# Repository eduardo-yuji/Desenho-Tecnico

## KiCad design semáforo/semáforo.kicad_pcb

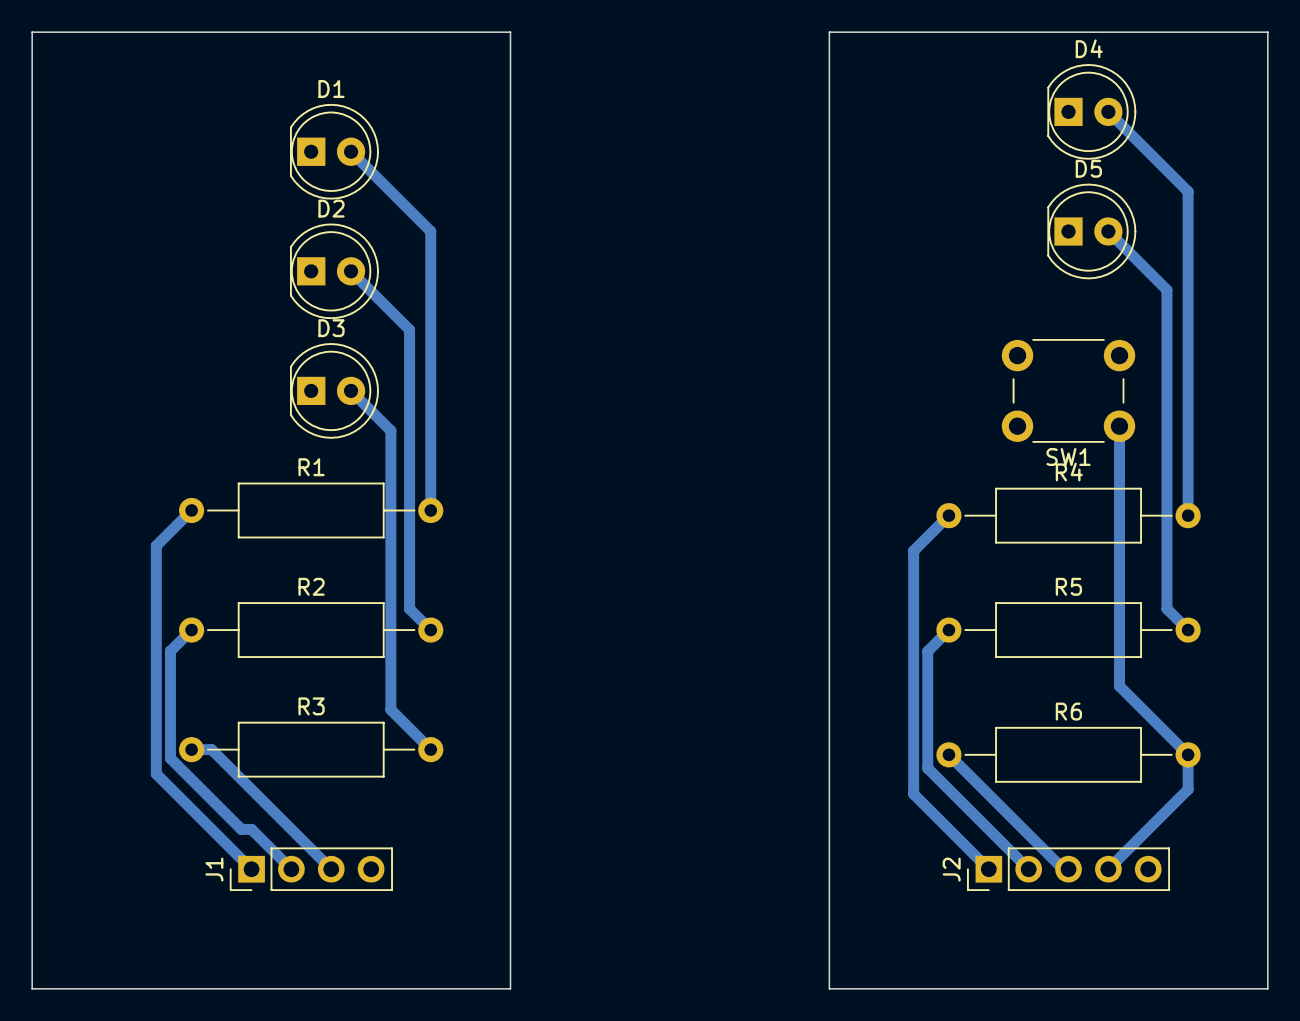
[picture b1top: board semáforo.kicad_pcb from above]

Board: 2 copper layers, 78.7 x 61.0 mm, 14 parts (0 on the bottom side), 13 nets.

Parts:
D1, D2, D3, D4, D5: LED; LED_D5.0mm
J1: Conn_01x04_Male; PinHeader_1x04_P2.54mm_Vertical
J2: Conn_01x05_Male; PinHeader_1x05_P2.54mm_Vertical
R1, R2, R3, R4, R5, R6: R; R_Axial_DIN0309_L9.0mm_D3.2mm_P15.24mm_Horizontal
SW1: SW_Push; SW_PUSH_6mm_H5mm

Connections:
GND: D1.1 (K), D2.1 (K), D3.1 (K), D4.1 (K), D5.1 (K), J1.4, J2.5, SW1.2
unnamed: D1.2 (A), R1.2
unnamed: D2.2 (A), R2.2
unnamed: D3.2 (A), R3.2
unnamed: J1.1, R1.1
unnamed: J1.2, R2.1
unnamed: J1.3, R3.1
unnamed: J2.1, R4.1
unnamed: D4.2 (A), R4.2
unnamed: J2.2, R5.1
unnamed: D5.2 (A), R5.2
unnamed: J2.3, R6.1
unnamed: J2.4, R6.2, SW1.1

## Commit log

2024-06-13 Xbox Logo
